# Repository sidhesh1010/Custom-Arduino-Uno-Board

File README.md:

#  Custom Arduino Uno Compatible PCB 

##  Overview

This project is a custom-designed Arduino Uno compatible PCB developed using KiCad. The design is based on the ATmega328P microcontroller and integrates multiple hardware modules such as motor driver, 
seven segment display, RGB LED, and user input components into a single compact board.

The goal of this project is to create a multifunctional embedded system board that extends the capabilities of a standard Arduino Uno by integrating additional peripherals directly on the PCB.

---

##  Objectives

* Design a complete Arduino-compatible PCB from scratch
* Integrate multiple modules into a single hardware platform
* Learn PCB routing, power distribution, and component placement
* Gain practical experience in embedded hardware design

---

##  Key Features

* ATmega328P microcontroller (main controller)
* On-board 5V regulated power supply using 7805
* Motor driver interface (L293D) for DC motor control
* Seven segment display driver (CD4511)
* RGB LED module for visual output
* Push button switches for user input
* Potentiometer for analog input
* ISP debug/programming header
* Compact PCB with organized routing and labeling

---

##  Functional Blocks

###  Power Supply Section

* DC input via power connector
* Reverse polarity protection diode
* 7805 voltage regulator for stable 5V output
* Filtering capacitors for noise reduction

---

###  Microcontroller Unit (ATmega328P)

* Central processing unit of the board
* External crystal oscillator for clock stability
* Decoupling capacitors for noise suppression
* Connected to all peripheral modules

---

###  Motor Driver Section

* L293D motor driver IC
* Supports control of DC motors
* Controlled via microcontroller digital pins

---

###  Seven Segment Display Section

* CD4511 BCD to 7-segment decoder
* Connected to MCU for numeric display output
* Current limiting resistors used for segment protection

---

###  RGB LED Module

* RGB LED with individual control lines
* Resistors for current limiting
* Can be controlled using PWM signals

---

###  Input Controls

* Push button switches for digital input
* Potentiometer connected to analog input (ADC)
* Useful for testing user interaction

---

###  Debug / Programming Header

* ISP header for programming ATmega328P
* Supports bootloader burning and firmware upload

---

##  Project Preview

###  Schematic Design

###  PCB Routing Layout

###  3D View

---

##  PCB Specifications

* Board Size: ~80mm × 50mm
* Mounting Holes: 4 (for enclosure support)
* Through-hole + SMD mixed design
* Clearly labeled silkscreen for easy debugging

---

##  Components Used

| Component          | Description            |
| ------------------ | ---------------------- |
| ATmega328P         | Main microcontroller   |
| 7805               | 5V voltage regulator   |
| L293D              | Motor driver IC        |
| CD4511             | 7-segment decoder      |
| Crystal Oscillator | Clock source           |
| Capacitors         | Filtering & decoupling |
| Resistors          | Current limiting       |
| RGB LED            | Visual output          |
| Push Buttons       | User input             |
| Potentiometer      | Analog input           |
| Connectors         | Power & I/O            |

---

##  Tools Used

* KiCad (Schematic + PCB Design)

---

##  Important Notes

* This is a **custom Arduino-compatible board**, not an official Arduino product
* Ensure correct power input (avoid over-voltage)
* Verify component orientation before powering the board
* Suitable for educational and prototyping purposes

---

##  Future Improvements

* Add USB-to-Serial interface (CH340 / FT232)
* Add onboard voltage regulator alternatives (switching regulator)
* Improve grounding with full ground plane
* Optimize routing for high-current paths
* Add protection circuits (fuse, reverse polarity protection)

---

##  Files Included

* `.kicad_pro` → Project configuration
* `.kicad_sch` → Schematic design
* `.kicad_pcb` → PCB layout

---

##  Learning Outcomes

This project demonstrates:

* Embedded system hardware design
* Multi-module PCB integration
* Power supply design
* Signal routing and layout optimization
* Practical use of KiCad for real-world projects

---

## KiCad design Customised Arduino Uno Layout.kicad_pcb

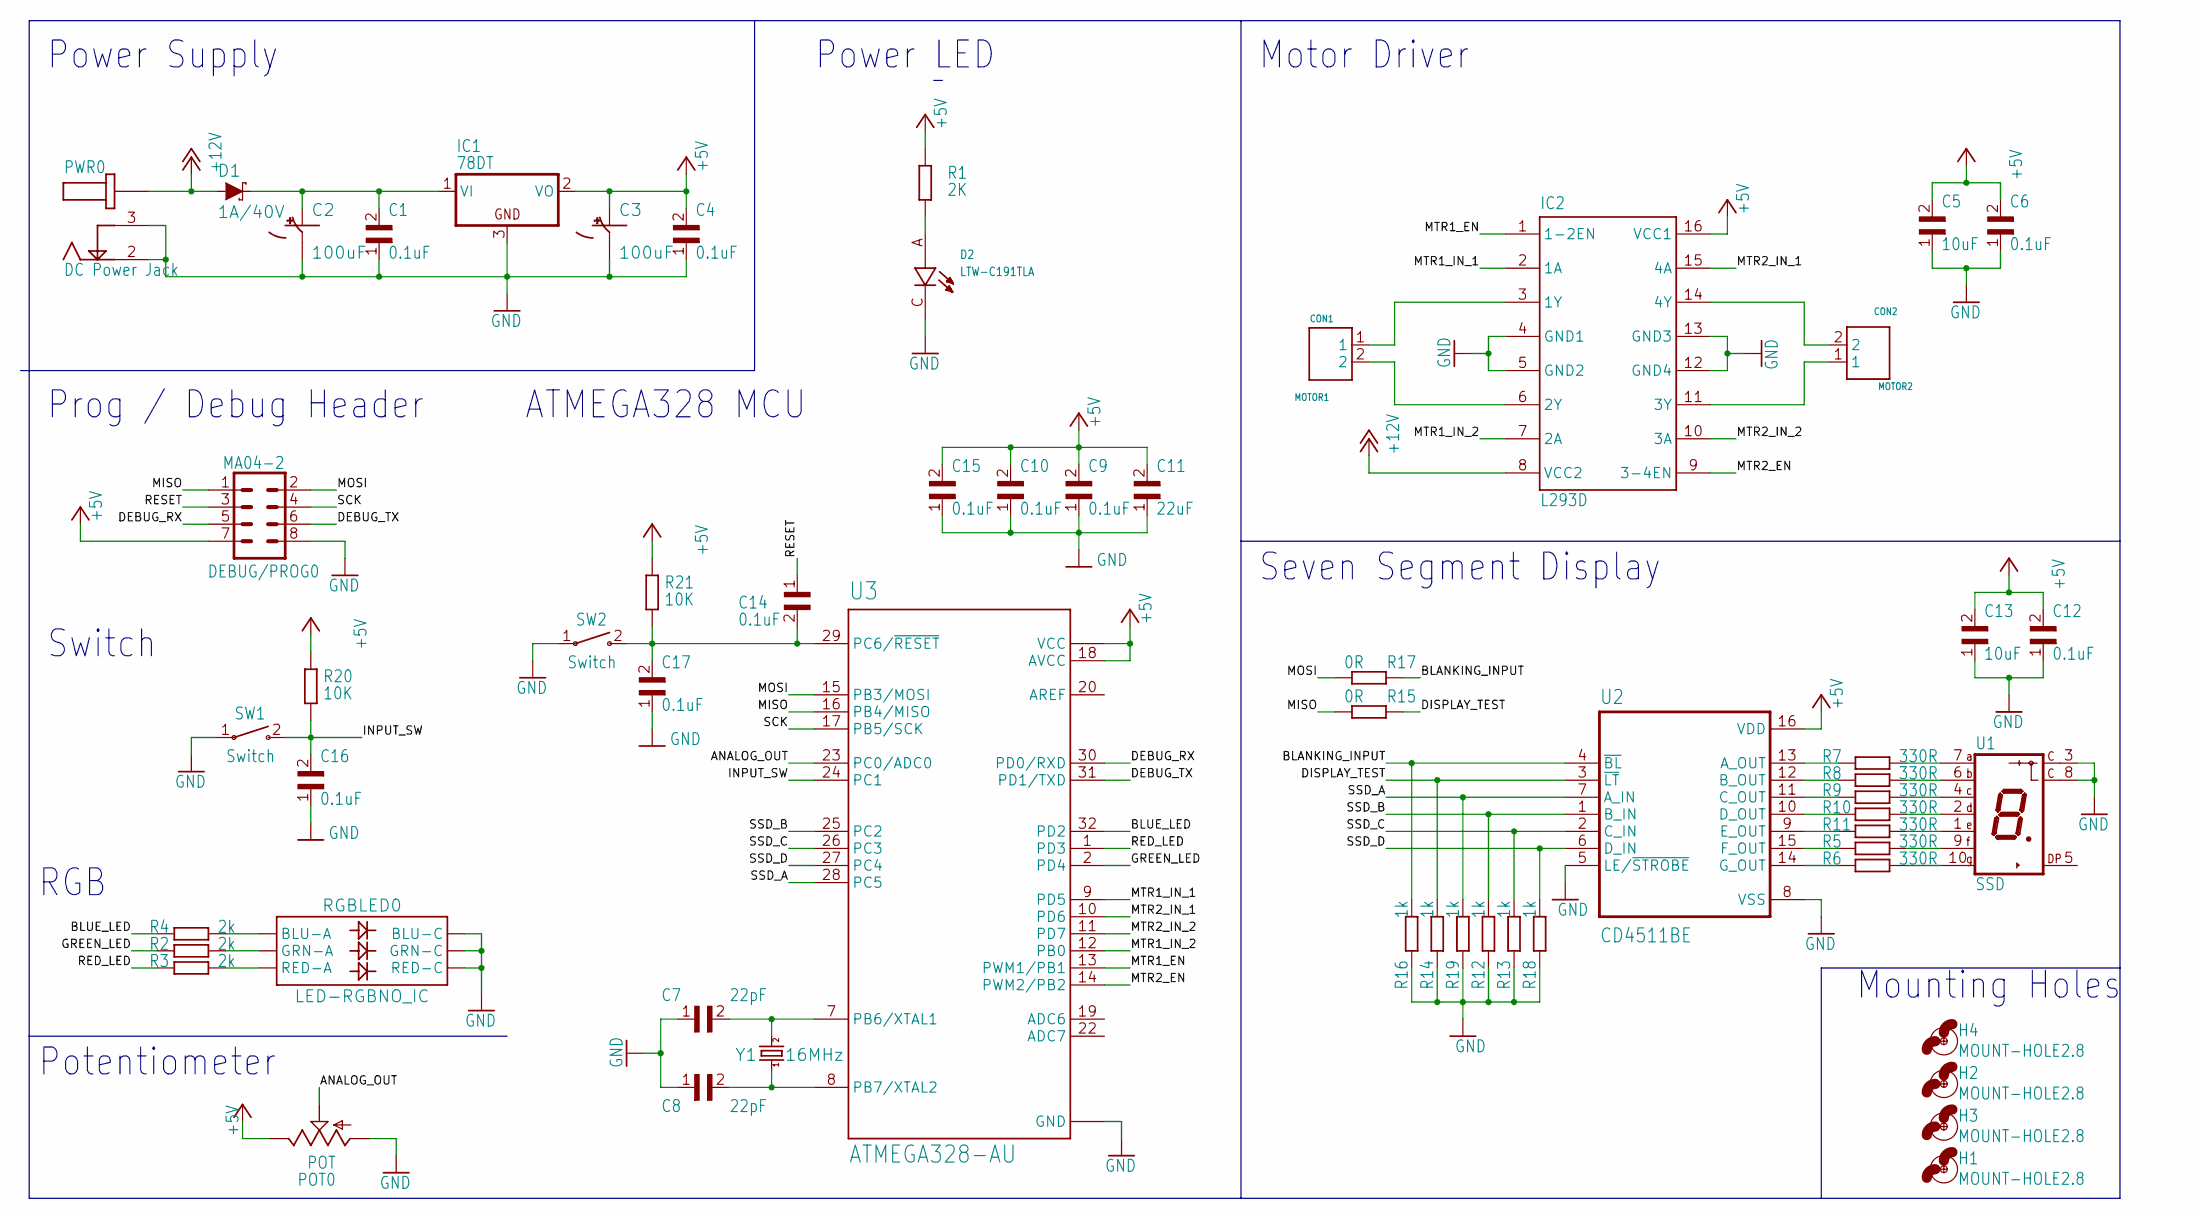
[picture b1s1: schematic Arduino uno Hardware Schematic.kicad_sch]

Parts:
C1, C4, C6, C9, C10, C12, C14, C15, C16, C17: 0.1uF; C0603
C2, C3: 100uF; CPOL-RADIAL-2.5MM-6.5MM
C5, C13: 10uF; C0603
C7, C8: 22pF; C0603
C11: 22uF; C0603
CON1: MOTOR1; CONN_282836-2
CON2: MOTOR2; CONN_282836-2
D1: 1A/40V; SMA-DIODE
D2: LTW-C191TLA; LEDC1608X65N
DEBUG/PROG0: MA04-2
H1, H2, H3, H4: MOUNT-HOLE2.8; 2,8
IC1: 78DT; TO252
IC2: L293D; DIL16
POT0: POT; S64W
PWR0: DC Power Jack; GCT_DCJ200-05-A-XX-X_REVA
R1: 2K; R0603
R2, R3, R4: 2k; R0603
R5, R6, R7, R8, R9, R10, R11: 330R; R0603
R12, R13, R14, R16, R18, R19: 1k; R0603
R15, R17: 0R; R0603
R20, R21: 10K; R0603
RGBLED0: LED-RGBNO_IC; LED-TRICOLOR-5050
SW1, SW2: Switch; SW_1437566-3
U1: SSD; LED_SC52-11HWA
U2: CD4511BE; DIP794W45P254L1969H508Q16
U3: ATMEGA328-AU; QFP80P900X900X120-32N
Y1: 16MHz; HC49US

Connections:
+5V: C3.1 (+), C4.2, C5.2, C6.2, C9.2, C10.2, C11.2, C12.2, C13.2, C15.2, DEBUG/PROG0.7, IC1.2 (VO), IC2.16 (VCC1), POT0.E, R1.2, R20.2, R21.2, U2.16 (VDD), U3.4 (VCC), U3.6 (VCC), U3.18 (AVCC)
+12V: D1.A, IC2.8 (VCC2), PWR0.1.1 (1), PWR0.1.2 (1)
ANALOG_OUT: POT0.S, U3.23 (PC0/ADC0)
BLANKING_INPUT: R16.2, R17.1, U2.4 (~BL)
BLUE_LED: R4.1, U3.32 (PD2)
DEBUG_RX: DEBUG/PROG0.5, U3.30 (PD0/RXD)
DEBUG_TX: DEBUG/PROG0.6, U3.31 (PD1/TXD)
DISPLAY_TEST: R14.2, R15.1, U2.3 (~LT)
GND: C1.1, C2.2 (-), C3.2 (-), C4.1, C5.1, C6.1, C7.1, C8.1, C9.1, C10.1, C11.1, C12.1, C13.1, C15.1, C16.1, C17.1, D2.C, DEBUG/PROG0.8, IC1.3 (GND), IC2.4 (GND1), IC2.5 (GND2), IC2.12 (GND4), IC2.13 (GND3), POT0.A, PWR0.2, PWR0.3, R12.1, R13.1, R14.1, R16.1, R18.1, R19.1, RGBLED0.4 (BLU-C), RGBLED0.5 (RED-C), RGBLED0.6 (GRN-C), SW1.1, SW2.1, U1.3 (C@1), U1.8 (C@2), U2.5 (LE/~STROBE), U2.8 (VSS), U3.3 (GND), U3.5 (GND), U3.21 (GND)
GREEN_LED: R2.1, U3.2 (PD4)
INPUT_SW: C16.2, R20.1, SW1.2, U3.24 (PC1)
MISO: DEBUG/PROG0.1, R15.2, U3.16 (PB4/MISO)
MOSI: DEBUG/PROG0.2, R17.2, U3.15 (PB3/MOSI)
MTR1_EN: IC2.1 (1-2EN), U3.13 (PWM1/PB1)
MTR1_IN_1: IC2.2 (1A), U3.9 (PD5)
MTR1_IN_2: IC2.7 (2A), U3.12 (PB0)
MTR2_EN: IC2.9 (3-4EN), U3.14 (PWM2/PB2)
MTR2_IN_1: IC2.15 (4A), U3.10 (PD6)
MTR2_IN_2: IC2.10 (3A), U3.11 (PD7)
unnamed: R3.2, RGBLED0.2 (RED-A)
unnamed: R2.2, RGBLED0.1 (GRN-A)
unnamed: R4.2, RGBLED0.3 (BLU-A)
unnamed: R7.1, U2.13 (A_OUT)
unnamed: R8.1, U2.12 (B_OUT)
unnamed: R9.1, U2.11 (C_OUT)
unnamed: R10.1, U2.10 (D_OUT)
unnamed: R11.1, U2.9 (E_OUT)
unnamed: R5.1, U2.15 (F_OUT)
unnamed: R6.1, U2.14 (G_OUT)
unnamed: R7.2, U1.7 (A)
unnamed: R8.2, U1.6 (B)
unnamed: R9.2, U1.4 (C)
unnamed: R10.2, U1.2 (D)
unnamed: R11.2, U1.1 (E)
unnamed: R5.2, U1.9 (F)
unnamed: R6.2, U1.10 (G)
unnamed: CON2.1, IC2.11 (3Y)
unnamed: D2.A, R1.1
unnamed: C1.2, C2.1 (+), D1.C, IC1.1 (VI)
unnamed: C8.2, U3.8 (PB7/XTAL2), Y1.1
unnamed: C7.2, U3.7 (PB6/XTAL1), Y1.2
unnamed: C14.2, C17.2, R21.1, SW2.2, U3.29 (PC6/~RESET)
unnamed: CON1.1, IC2.3 (1Y)
unnamed: CON1.2, IC2.6 (2Y)
unnamed: CON2.2, IC2.14 (4Y)
RED_LED: R3.1, U3.1 (PD3)
RESET: C14.1, DEBUG/PROG0.3
SCK: DEBUG/PROG0.4, U3.17 (PB5/SCK)
SSD_A: R19.2, U2.7 (A_IN), U3.28 (PC5)
SSD_B: R12.2, U2.1 (B_IN), U3.25 (PC2)
SSD_C: R13.2, U2.2 (C_IN), U3.26 (PC3)
SSD_D: R18.2, U2.6 (D_IN), U3.27 (PC4)

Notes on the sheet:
Seven Segment Display
Mounting Holes
RGB
Motor Driver
Power LED
ATMEGA328 MCU
Switch
Prog / Debug Header
Power Supply
Potentiometer

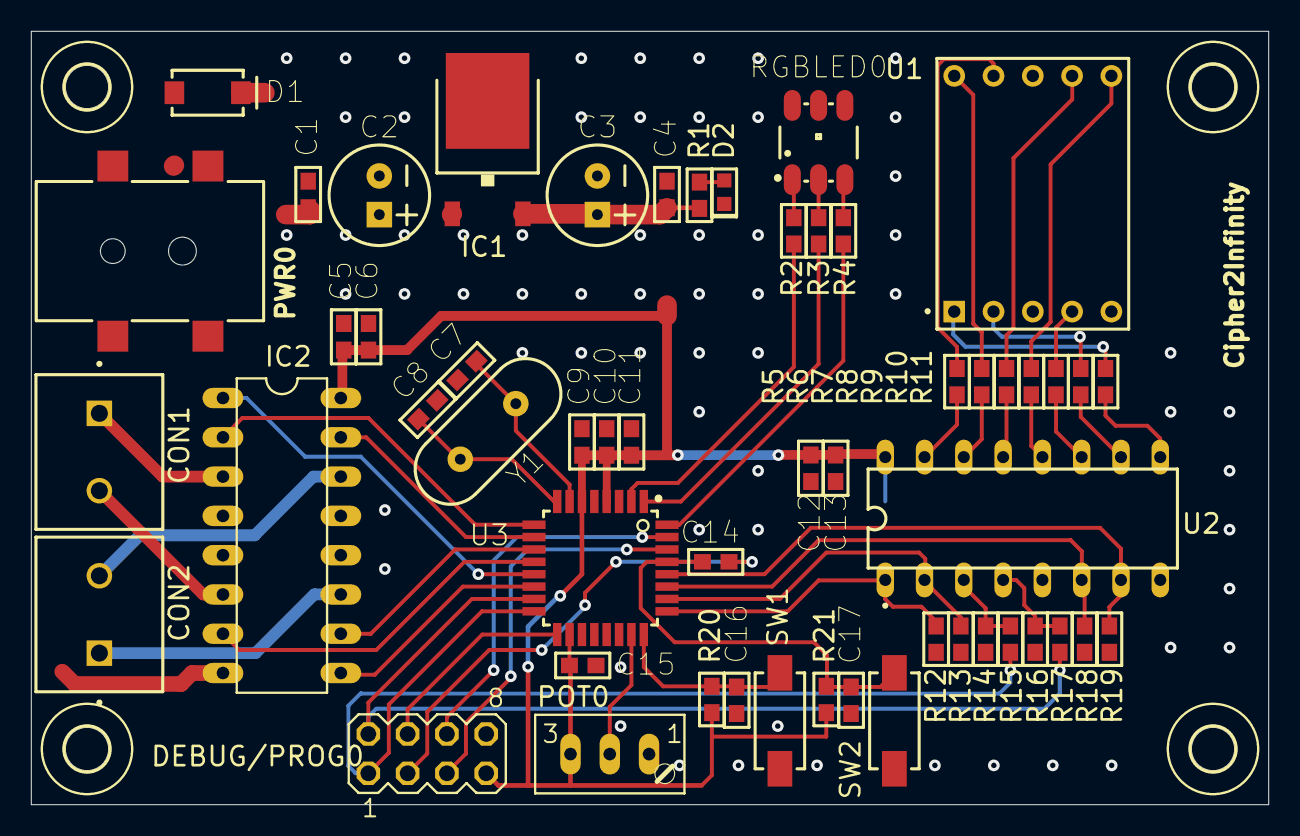
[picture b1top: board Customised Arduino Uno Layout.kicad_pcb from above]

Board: 2 copper layers, 80.0 x 50.0 mm, 58 parts (0 on the bottom side), 52 nets.

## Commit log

2026-04-18 Add files via upload
    Update README with detailed hardware design documentation
2026-04-18 Add files via upload
    Add project images
2026-04-18 Update README.md
    Add project images and update README
2026-04-18 Rename Back View.JPG to Back_View.JPG
2026-04-18 Rename Front View.JPG to Front_View.JPG
2026-04-18 Rename Side View.JPG to Side_View.JPG
